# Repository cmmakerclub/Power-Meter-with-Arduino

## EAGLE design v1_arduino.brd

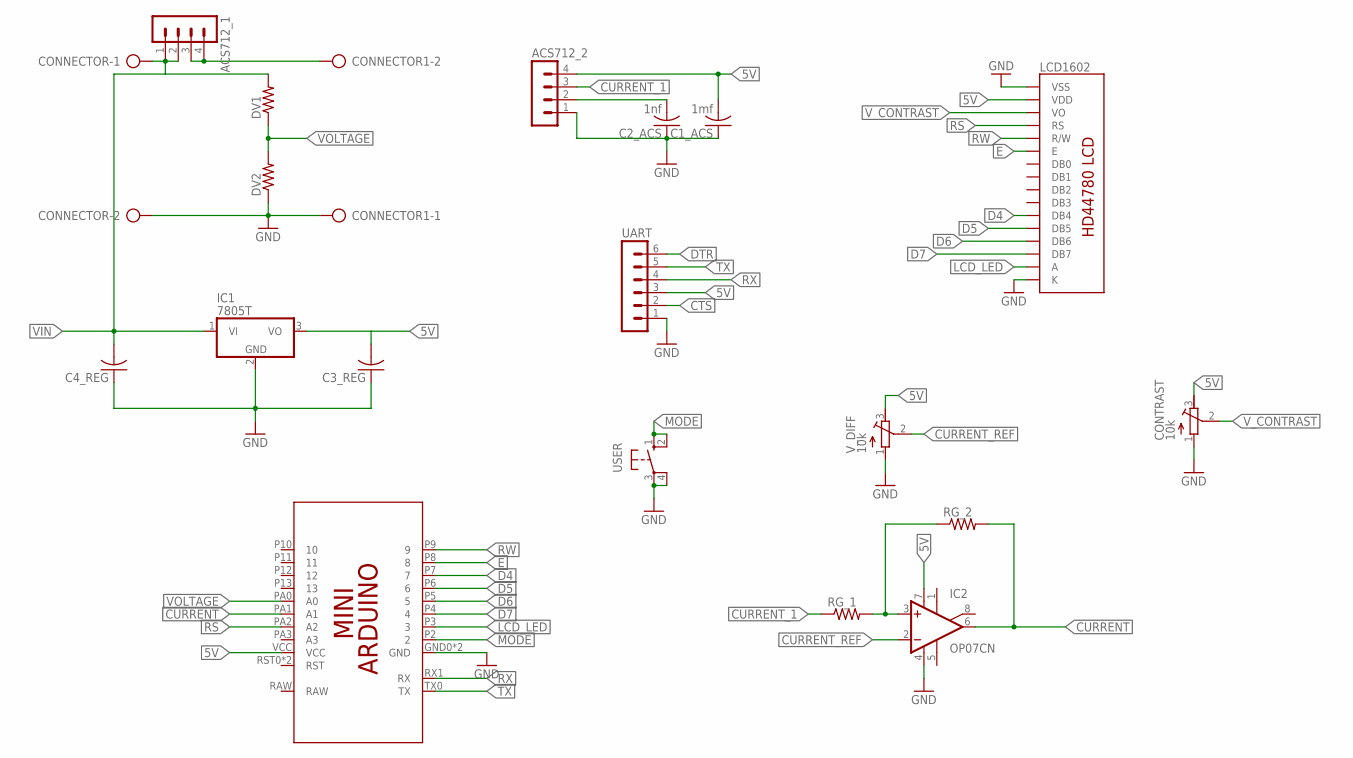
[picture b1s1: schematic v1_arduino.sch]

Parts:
ACS712_1, ACS712_2: MA04-1
C1_ACS: 1mf; C0805K
C2_ACS: 1nf; C0805K
C3_REG, C4_REG: C-USC0805K; C0805K
CONNECTOR, CONNECTOR1: AK500/2-H
CONTRAST: 10k; RTRIM3296W
DV1, DV2: R-US_M0805; M0805
IC1: 7805T; TO220H
IC2: OP07CN; DIL08
LCD1602: LCD-HD447803-HOLES16X2-3-HOLES; LCD-16X2-3HOLES
RG_1, RG_2: R-US_M0805; M0805
U$1: ARDUINO_PRO_MINI
UART: MA06-1
USER: 40-XX; B3F-40XX
V_DIFF: 10k; RTRIM3296W

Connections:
5V: ACS712_2.4, C1_ACS.2, C3_REG.2, CONTRAST.3 (A), IC1.3 (VO), IC2.7 (V+), LCD1602.2 (VDD), U$1.VCC, UART.3, V_DIFF.3 (A)
CTS: UART.2
CURRENT: IC2.6 (OUT), RG_2.2, U$1.PA1 (A1)
CURRENT_1: ACS712_2.3, RG_1.1
CURRENT_REF: IC2.2 (-IN), V_DIFF.2 (S)
D4: LCD1602.11 (DB4), U$1.P7 (7)
D5: LCD1602.12 (DB5), U$1.P6 (6)
D6: LCD1602.13 (DB6), U$1.P5 (5)
D7: LCD1602.14 (DB7), U$1.P4 (4)
DTR: UART.6
E: LCD1602.6 (E), U$1.P8 (8)
GND: ACS712_2.1, C1_ACS.1, C2_ACS.1, C3_REG.1, C4_REG.1, CONNECTOR.2, CONNECTOR1.1, CONTRAST.1 (E), DV2.1, IC1.2 (GND), IC2.4 (V-), LCD1602.1 (VSS), LCD1602.16 (K), U$1.GND0 (GND), U$1.GND1 (GND), UART.1, USER.3, USER.4 (P1), V_DIFF.1 (E)
LCD_LED: LCD1602.15 (A), U$1.P3 (3)
MODE: U$1.P2 (2), USER.1 (S), USER.2 (S1)
unnamed: ACS712_1.3, ACS712_1.4, CONNECTOR1.2
unnamed: IC2.3 (+IN), RG_1.2, RG_2.1
unnamed: ACS712_2.2, C2_ACS.2
RS: LCD1602.4 (RS), U$1.PA2 (A2)
RW: LCD1602.5 (R/W), U$1.P9 (9)
RX: U$1.RX1 (RX), UART.4
TX: U$1.TX0 (TX), UART.5
VIN: ACS712_1.1, ACS712_1.2, C4_REG.2, CONNECTOR.1, DV1.2, IC1.1 (VI)
VOLTAGE: DV1.1, DV2.2, U$1.PA0 (A0)
V_CONTRAST: CONTRAST.2 (S), LCD1602.3 (VO)

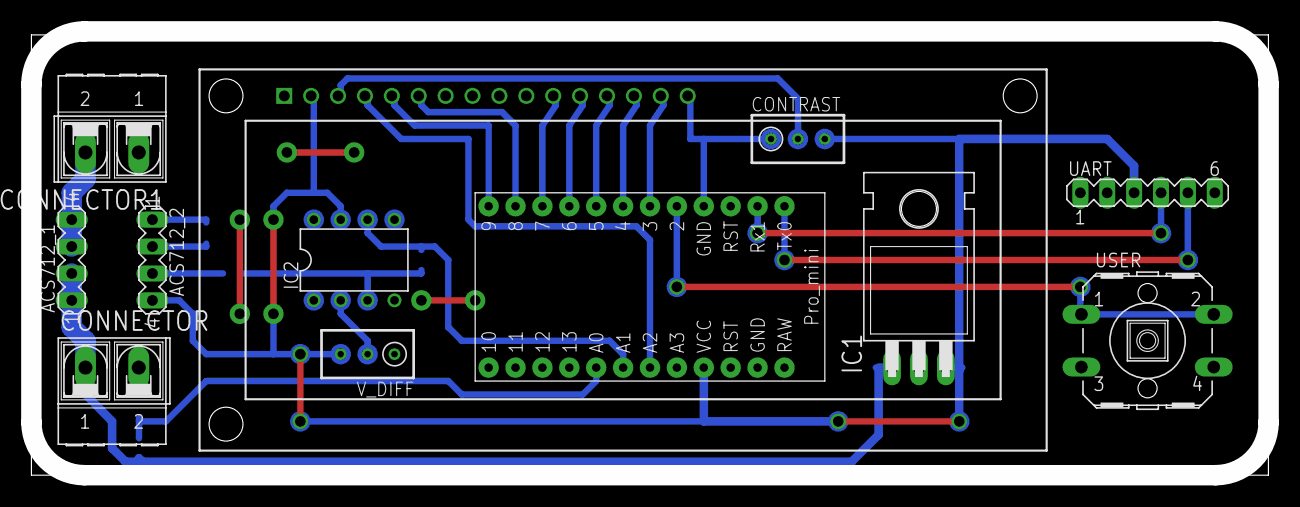
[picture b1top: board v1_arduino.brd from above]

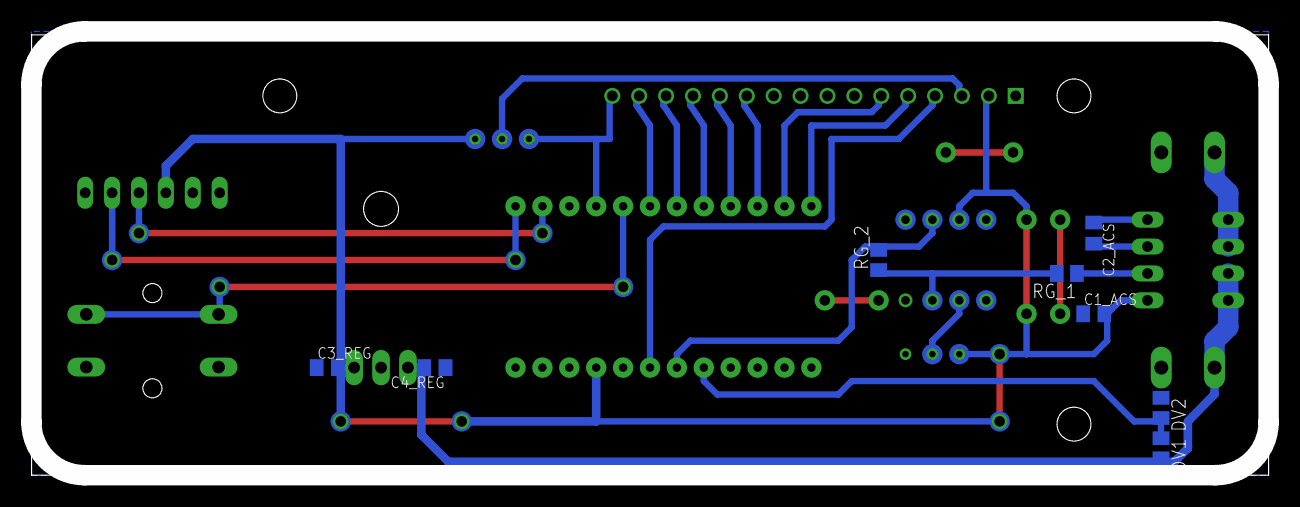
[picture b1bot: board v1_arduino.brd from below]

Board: 2 copper layers, 116.8 x 41.9 mm, 20 parts (8 on the bottom side), 22 nets.

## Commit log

2014-12-28 first version
